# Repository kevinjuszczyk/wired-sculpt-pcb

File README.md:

# Design Files for Wired Sculpt Conversion Board
Modified for fabrication and assembly by JLCPCB.  
Components in the BOM with an LCSC number can be placed by JLCPCB.  
Remaining components can be ordered from Digikey and hand assembled.  
This design includes support for lighting the green LED and reading the media/Fn switch.

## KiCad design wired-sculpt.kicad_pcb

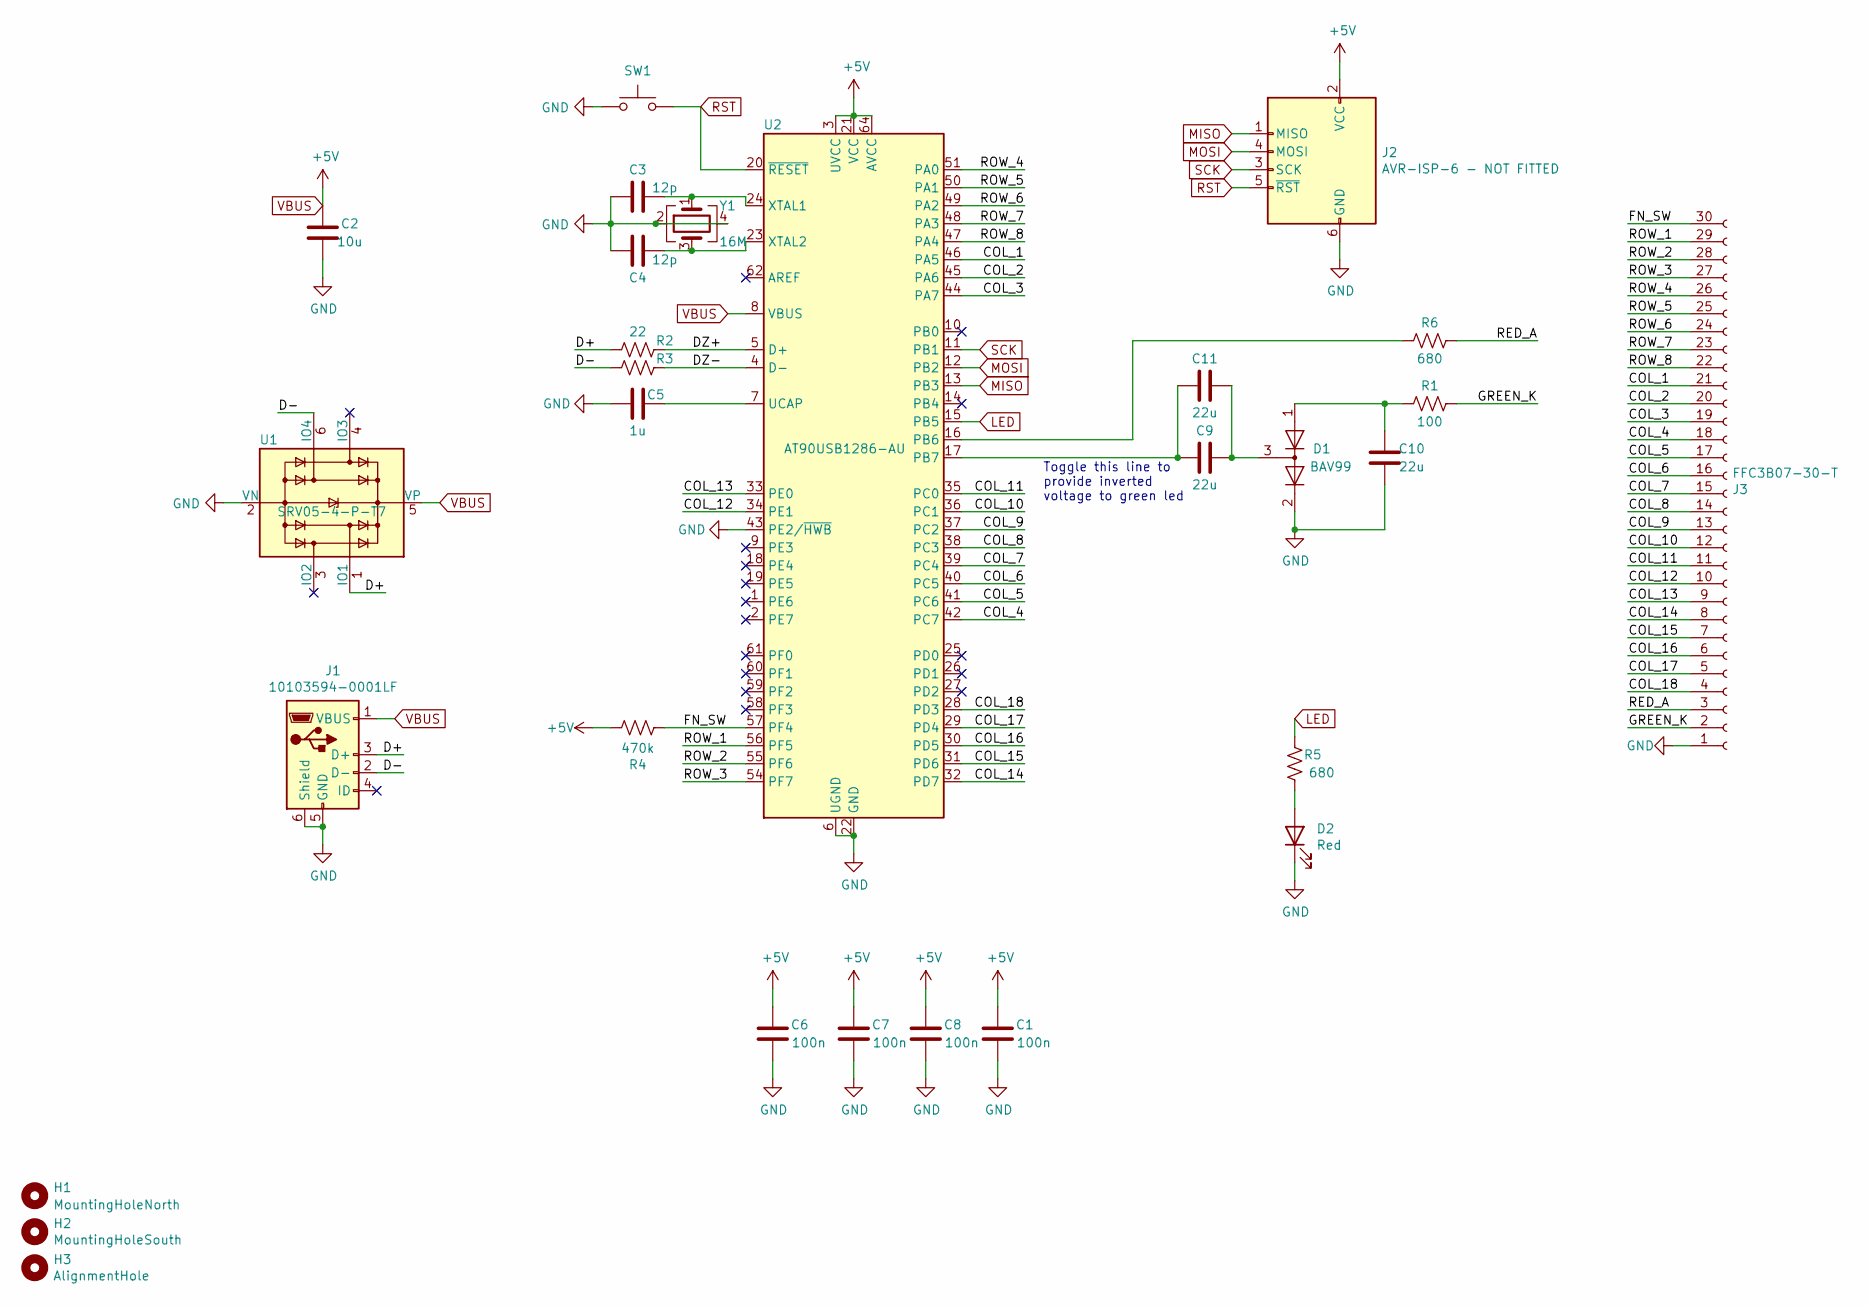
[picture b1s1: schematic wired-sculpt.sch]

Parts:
C1, C6, C7, C8: 100n; C_0603_1608Metric; Mfr_part CC0603KRX7R9BB104; LCSC C14663
C2: 10u; C_0603_1608Metric; Mfr_part CL10A106KP8NNNC; LCSC C19702
C3, C4: 12p; C_0603_1608Metric; Mfr_part CL10C120JB8NNNC; LCSC C38523
C5: 1u; C_0603_1608Metric; Mfr_part CL10A105KB8NNNC; LCSC C15849
C9, C10, C11: 22u; C_0603_1608Metric; Mfr_part CL10A226MQ8NRNC; LCSC C59461
D1: BAV99; SOT-23; Mfr_part BAV99,215; LCSC C2500
D2: Red; LED_0603_1608Metric_Castellated; Mfr_part KT-0603R; LCSC C2286
H1: MountingHoleNorth; MountingHole_2.2mm_M2
H2: MountingHoleSouth; MountingHole_2.2mm_M2
H3: AlignmentHole; MountingHole_2.7mm
J1: 10103594-0001LF; USB_Micro-B_Molex-105017-0001
J2: AVR-ISP-6 - NOT FITTED; IDC-Header_2x03_P2.54mm_Horizontal
J3: FFC3B07-30-T; TE_3-84952-0_1x30-1MP_P1.0mm_Horizontal
R1: 100; R_0603_1608Metric; Mfr_part 0603WAF1000T5E; LCSC C22775
R2, R3: 22; R_0402_1005Metric; Mfr_part 0402WGF220JTCE; LCSC C25092
R4: 470k; R_0603_1608Metric; Mfr_part 0603WAF4703T5E; LCSC C23178
R5, R6: 680; R_0603_1608Metric; Mfr_part 0603WAF6800T5E; LCSC C23228
SW1: MJTP1117; SW_Tactile_SPST_Angled_MJTP1117; Mfr_part MJTP1117
U1: SRV05-4-P-T7; SOT-23-6; Mfr_part SRV05-4-P-T7; LCSC C85364
U2: AT90USB1286-AU; TQFP-64_14x14mm_P0.8mm; Mfr_part AT90USB1286-AU; LCSC C619147
Y1: 16M; Crystal_SMD_3225-4Pin_3.2x2.5mm; Mfr_part X322516MLB4SI; LCSC C13738

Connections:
/COL_1: J3.21, U2.46 (PA5)
/COL_2: J3.20, U2.45 (PA6)
/COL_3: J3.19, U2.44 (PA7)
/COL_4: J3.18, U2.42 (PC7)
/COL_5: J3.17, U2.41 (PC6)
/COL_6: J3.16, U2.40 (PC5)
/COL_7: J3.15, U2.39 (PC4)
/COL_8: J3.14, U2.38 (PC3)
/COL_9: J3.13, U2.37 (PC2)
/COL_10: J3.12, U2.36 (PC1)
/COL_11: J3.11, U2.35 (PC0)
/COL_12: J3.10, U2.34 (PE1)
/COL_13: J3.9, U2.33 (PE0)
/COL_14: J3.8, U2.32 (PD7)
/COL_15: J3.7, U2.31 (PD6)
/COL_16: J3.6, U2.30 (PD5)
/COL_17: J3.5, U2.29 (PD4)
/COL_18: J3.4, U2.28 (PD3)
/D+: J1.3 (D+), R2.2, U1.1 (IO1)
/D-: J1.2 (D-), R3.2, U1.6 (IO4)
/DZ+: R2.1, U2.5 (D+)
/DZ-: R3.1, U2.4 (D-)
/FN_SW: J3.30, R4.2, U2.57 (PF4)
/GREEN_K: J3.2, R1.1
/RED_A: J3.3, R6.1
/ROW_1: J3.29, U2.56 (PF5)
/ROW_2: J3.28, U2.55 (PF6)
/ROW_3: J3.27, U2.54 (PF7)
/ROW_4: J3.26, U2.51 (PA0)
/ROW_5: J3.25, U2.50 (PA1)
/ROW_6: J3.24, U2.49 (PA2)
/ROW_7: J3.23, U2.48 (PA3)
/ROW_8: J3.22, U2.47 (PA4)
GND: C1.1, C2.1, C3.2, C4.2, C5.2, C6.1, C7.1, C8.1, C10.1, D1.2 (A), D2.1 (K), J1.5 (GND), J1.6 (Shield), J2.6 (GND), J3.1, SW1.1, U1.2 (VN), U2.6 (UGND), U2.22 (GND), U2.43 (PE2/~HWB), U2.53 (GND), U2.63 (GND), Y1.2, Y1.4
LED: R5.2, U2.15 (PB5)
MISO: J2.1 (MISO), U2.13 (PB3)
MOSI: J2.4 (MOSI), U2.12 (PB2)
unnamed: C3.1, U2.24 (XTAL1), Y1.1
unnamed: C4.1, U2.23 (XTAL2), Y1.3
unnamed: C5.1, U2.7 (UCAP)
unnamed: C10.2, D1.1 (K), R1.2
unnamed: C9.1, C11.1, D1.3 (K)
unnamed: C9.2, C11.2, U2.17 (PB7)
unnamed: D2.2 (A), R5.1
unnamed: R6.2, U2.16 (PB6)
RST: J2.5 (~RST), SW1.2, U2.20 (~RESET)
SCK: J2.3 (SCK), U2.11 (PB1)
VBUS: C1.2, C2.2, C6.2, C7.2, C8.2, J1.1 (VBUS), J2.2 (VCC), R4.1, U1.5 (VP), U2.3 (UVCC), U2.8 (VBUS), U2.21 (VCC), U2.52 (VCC), U2.64 (AVCC)

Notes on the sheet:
Toggle this line to provide inverted voltage to green led

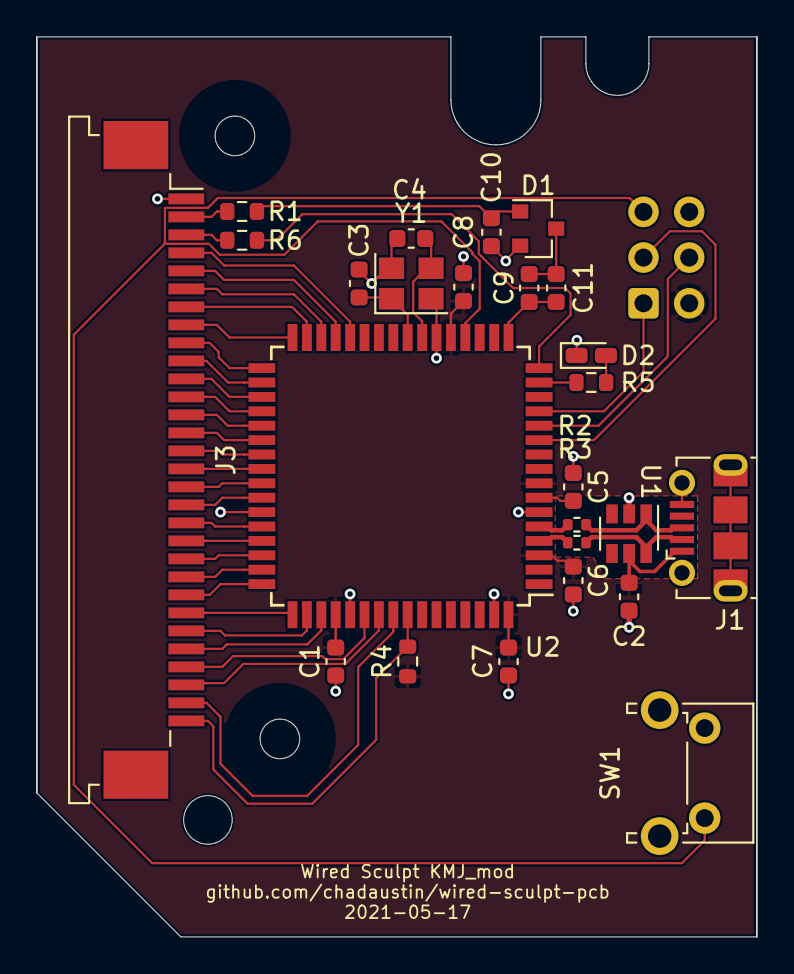
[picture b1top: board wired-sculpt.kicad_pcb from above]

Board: 2 copper layers, 40.0 x 50.0 mm, 29 parts (1 on the bottom side), 48 nets.

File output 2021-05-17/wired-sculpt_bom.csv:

"Comment","Designator","Footprint","Desc","LCSC","Mfr","MfrPN","Link"
"10u","C2","Capacitor_SMD:C_0603_1608Metric","10uF ±10% 10V X5R","C19702","Samsung Electro-Mechanics","CL10A106KP8NNNC",
"12p","C3,C4","Capacitor_SMD:C_0603_1608Metric","12pF ±5% 50V C0G 0603","C38523","Samsung Electro-Mechanics","CL10C120JB8NNNC",
"1u","C5","Capacitor_SMD:C_0603_1608Metric","1uF ±10% 50V X5R 0603","C15849","Samsung Electro-Mechanics","CL10A105KB8NNNC",
"100n","C6,C7,C8,C1","Capacitor_SMD:C_0603_1608Metric","100nF ±10% 50V X7R 0603 ","C14663","YAGEO","CC0603KRX7R9BB104",
"22u","C9,C10,C11","Capacitor_SMD:C_0603_1608Metric","22uF ±20% 6.3V X5R 0603","C59461","Samsung Electro-Mechanics","CL10A226MQ8NRNC",
"BAV99","D1","Package_TO_SOT_SMD:SOT-23","Switching Diode 100V 125mA 1.25V @ 150mA 4ns SOT-23(SOT-23-3)","C2500","Nexperia","BAV99,215",
"Red","D2","LED_SMD:LED_0603_1608Metric_Castellated","Light Emitting Diodes (LED) Red 520~625nm 90~100mcd@20mA Top View 0603","C2286","Hubei KENTO Elec","KT-0603R",
"MountingHoleNorth","H1","MountingHole:MountingHole_2.2mm_M2",,,,,
"MountingHoleSouth","H2","MountingHole:MountingHole_2.2mm_M2",,,,,
"AlignmentHole","H3","MountingHole:MountingHole_2.7mm",,,,,
"10103594-0001LF","J1","Connector_USB:USB_Micro-B_Molex-105017-0001","CONN RCPT USB2.0 MICRO B SMD R/A",,"Molex",1050170001,"https://www.digikey.com/en/products/detail/molex/1050170001/2350885"
"AVR-ISP-6 - NOT FITTED","J2","Connector_IDC:IDC-Header_2x03_P2.54mm_Horizontal",,,,,
"FFC3B07-30-T","J3","Connector_FFC-FPC:TE_3-84952-0_1x30-1MP_P1.0mm_Horizontal","CONN FPC BOTTOM 30POS 1.00MM R/A",,"TE Connectivity AMP Connectors","3-84952-0","https://www.digikey.com/en/products/detail/te-connectivity-a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"
"100","R1","Resistor_SMD:R_0603_1608Metric","100Ω ±1% 1/10W ±200ppm/°C 0603","C22775","UNI-ROYAL(Uniroyal Elec)","0603WAF1000T5E",
"22","R2,R3","Resistor_SMD:R_0402_1005Metric","22Ω ±1% 1/16W ±200ppm/℃ 0402","C25092","UNI-ROYAL(Uniroyal Elec)","0402WGF220JTCE",
"470k","R4","Resistor_SMD:R_0603_1608Metric","470kΩ ±1% 0.1W ±100ppm/℃ 0603","C23178","UNI-ROYAL(Uniroyal Elec)","0603WAF4703T5E",
"680","R5,R6","Resistor_SMD:R_0603_1608Metric","680Ω ±1% 0.1W ±100ppm/℃ 0603","C23228","UNI-ROYAL(Uniroyal Elec)","0603WAF6800T5E",
"MJTP1117","SW1","kmj_custom:SW_Tactile_SPST_Angled_MJTP1117","SWITCH TACTILE SPST-NO 0.05A 12V",,"APEM Inc. ","MJTP1117 ","https://www.digikey.com/en/products/detail/apem-inc/MJTP1117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"
"SRV05-4-P-T7","U1","Package_TO_SOT_SMD:SOT-23-6","TVS SOT-23-6","C85364","ProTek Devices","SRV05-4-P-T7",
"AT90USB1286-AU","U2","Package_QFP:TQFP-64_14x14mm_P0.8mm","TQFP-64 MCU","C619147","Microchip Tech","AT90USB1286-AU",
"16M","Y1","Crystal:Crystal_SMD_3225-4Pin_3.2x2.5mm","SMD Crystal Resonators 16MHz ±10ppm SMD-3225_4P","C13738","Yangxing Tech","X322516MLB4SI",

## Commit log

2021-05-25 modified for fabrication and assembly by JLCPCB
